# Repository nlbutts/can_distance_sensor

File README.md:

# I'm Not Touching You

This is a small CAN based Time-of-Flight (TOF) sensor. It determines the distance
to an object and sends the resulting message on the CAN bus.

# Design
The block diagram is shown below. The design consists of an input buck regulator.
The regulator should be good up to 24V, but was designed to work at 12V. There
is reverse battery protection, so it should handle accidentially connecting
the battery up in reverse.

The buck generates 5V which is used for the CAN transceiver. The 5V is fed
to two LDO's to generate 3.3V for the processor and 2.8V for the TOF sensor.

There are two status LEDs on the board. An STM32G431 processor powers everything.

There are three user accessible connectors:
Main J3:
| Pin | Use |
| -- | -- |
| 1 | Power |
| 2 | Ground |
| 3 | CAN High |
| 4 | CAN Low |

The mate is a **JST PHR-4**

There is a standard USB Micro B connector that connects to a PC. It enumerates
as a serial port.

# Software
The software uses the STM32CubeIDE to build the code. I really wanted to use CMake with the CubeMX tool,
but I was having trouble getting the code to work correctly. So CudeIDE for the win.

The code is SUPER simple. It just reads the TOF sensor once every 100 ms and sends out a CAN message.

The CAN message is defined as:
| Byte | Definition |
| ---- | --- |
| 1 | API Status |
| 2-3 | distance in mm |
| 4-5 | ambient Mcps |
| 6-7 | signal Mcps |

The **API Status** is the not well defined. If the value is zero, the distance is valid.
The distance is in millimeters.
The Ambient and Signal values are in Millions of Chips Per Second.

The CAN ID is based on the WPILib CAN interface:

Device Type is Misc (10)
Manufacturer is 20
API Class is Status (5)
API Index is 0
Device Number is currently 0 (need to figure out how to have several of these on the bus)

## SWD Debug
It is assumed you are using a JLink and it is installed in **/opt/SEGGER/JLink**
In the scripts directory:
1) Run **gdbstart.sh** in one terminal
2) Run debug.sh in other terminal. You now have the full power of GDB at your literial finger tips

## Firmware upgrade
There is no ability to upgrade the firmware right now. It will be fixed in future PCB rev.
Currently you have to JTAG/SWD the firmware.

# Potential other parts
STM32G0:
https://jlcpcb.com/partdetail/STMicroelectronics-STM32G0B1CBT6/C2847904
Can we use a M0???

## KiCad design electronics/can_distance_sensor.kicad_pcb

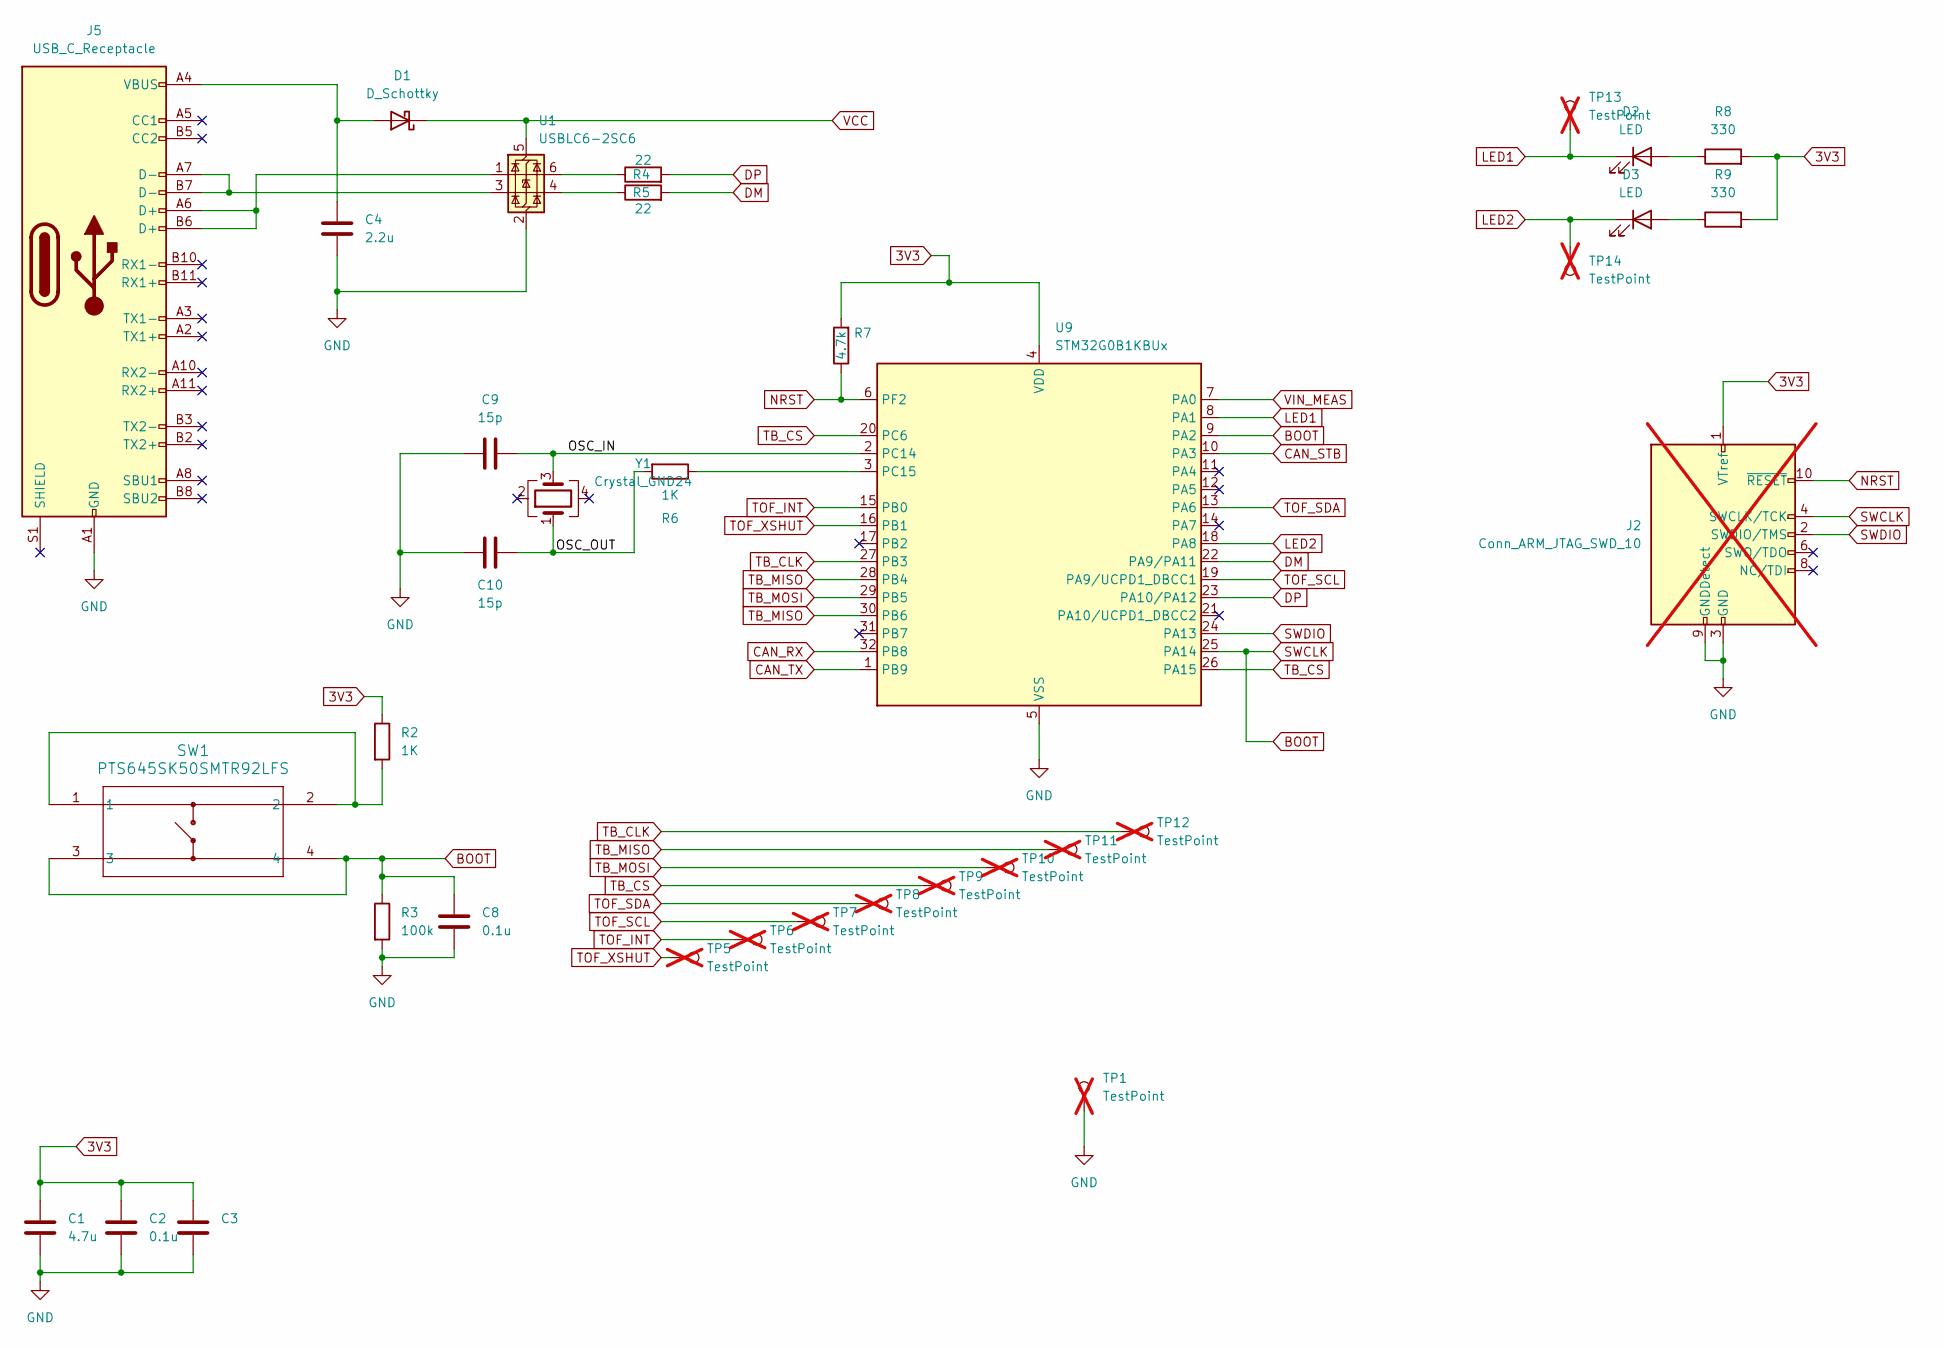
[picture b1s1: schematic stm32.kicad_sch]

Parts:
C1: 4.7u; C_0603_1608Metric; JLCPCB C19666
C2, C3, C8: 0.1u; C_0402_1005Metric; JLCPCB C1525
C4: 2.2u; C_0603_1608Metric; JLCPCB C23630
C9, C10: 15p; C_0402_1005Metric; JLCPCB C1548
D1: D_Schottky; D_SOD-123; Digikey B0540W-FDICT-ND
D2, D3: LED; LED_0603_1608Metric; JLCPCB C2286
J2: Conn_ARM_JTAG_SWD_10; Tag-Connect_TC2050-IDC-NL_2x05_P1.27mm_Vertical_with_bottom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; not fitted
J5: USB_C_Receptacle; CONN_105450-0101_MOL; JLCPCB C134092
R2, R6: 1K; R_0402_1005Metric; JLCPCB C11702
R3: 100k; R_0402_1005Metric; JLCPCB C25741
R4, R5: 22; R_0402_1005Metric; JLCPCB C25092
R7: 4.7k; R_0402_1005Metric; JLCPCB C25900
R8, R9: 330; R_0402_1005Metric; JLCPCB C25104
SW1: PTS645SK50SMTR92LFS; PTS645SK50SMTR92LFS_CNK; JLCPCB C221872
TP1, TP5, TP6, TP7, TP8, TP9, TP10, TP11, TP12, TP13, TP14: TestPoint; TestPoint_Pad_D1.0mm; not fitted
U1: USBLC6-2SC6; SOT-23-6; JLCPCB C7519
U9: STM32G0B1KBUx; QFN-32-1EP_5x5mm_P0.5mm_EP3.45x3.45mm; JLCPCB C5159549
Y1: Crystal_GND24; Crystal_SMD_3225-4Pin_3.2x2.5mm; JLCPCB C156247

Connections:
3V3: C1.1, C2.1, C3.1, J2.1 (VTref), R2.1, R7.2, R8.2, R9.2, U9.4 (VDD); also elsewhere on the board
/STM32/OSC_IN: C9.2, U9.2 (PC14), Y1.3
/STM32/OSC_OUT: C10.2, R6.2, Y1.1
BOOT: C8.1, J2.4 (SWCLK/TCK), R3.1, SW1.3, SW1.4, U9.9 (PA2), U9.25 (PA14)
CAN_RX: U9.32 (PB8); also elsewhere on the board
CAN_STB: U9.10 (PA3); also elsewhere on the board
CAN_TX: U9.1 (PB9); also elsewhere on the board
DM: R5.2, U9.22 (PA9/PA11)
DP: R4.2, U9.23 (PA10/PA12)
GND: C1.2, C2.2, C3.2, C4.1, C8.2, C9.1, C10.1, J2.3 (GND), J2.5 (GND), J2.9 (GNDDetect), J5.A1 (GND), J5.A12 (GND), J5.B1 (GND), J5.B12 (GND), R3.2, TP1.1, U1.2 (GND), U9.5 (VSS), U9.33 (VSS); also elsewhere on the board
LED1: D2.1 (K), TP13.1, U9.8 (PA1)
LED2: D3.1 (K), TP14.1, U9.18 (PA8)
NRST: J2.10 (~RESET), R7.1, U9.6 (PF2)
unnamed: C4.2, D1.2 (A), J5.A4 (VBUS), J5.A9 (VBUS), J5.B4 (VBUS), J5.B9 (VBUS)
unnamed: D2.2 (A), R8.1
unnamed: D3.2 (A), R9.1
unnamed: J5.A6 (D+), J5.B6 (D+), U1.1 (I/O1)
unnamed: J5.A7 (D-), J5.B7 (D-), U1.3 (I/O2)
unnamed: R2.2, SW1.1, SW1.2
unnamed: R4.1, U1.6 (I/O1)
unnamed: R5.1, U1.4 (I/O2)
unnamed: R6.1, U9.3 (PC15)
SWDIO: J2.2 (SWDIO/TMS), U9.24 (PA13)
TB_ABS: TP11.1, U9.28 (PB4), U9.30 (PB6); also elsewhere on the board
TB_CLK: TP12.1, U9.27 (PB3); also elsewhere on the board
TB_CS: TP9.1, U9.20 (PC6), U9.26 (PA15); also elsewhere on the board
TB_MOSI: TP10.1, U9.29 (PB5); also elsewhere on the board
TOF_INT: TP6.1, U9.15 (PB0); also elsewhere on the board
TOF_SCL: TP7.1, U9.19 (PA9/UCPD1_DBCC1); also elsewhere on the board
TOF_SDA: TP8.1, U9.13 (PA6); also elsewhere on the board
TOF_XSHUT: TP5.1, U9.16 (PB1); also elsewhere on the board
VCC: D1.1 (K), U1.5 (VBUS); also elsewhere on the board
VIN_MEAS: U9.7 (PA0); also elsewhere on the board

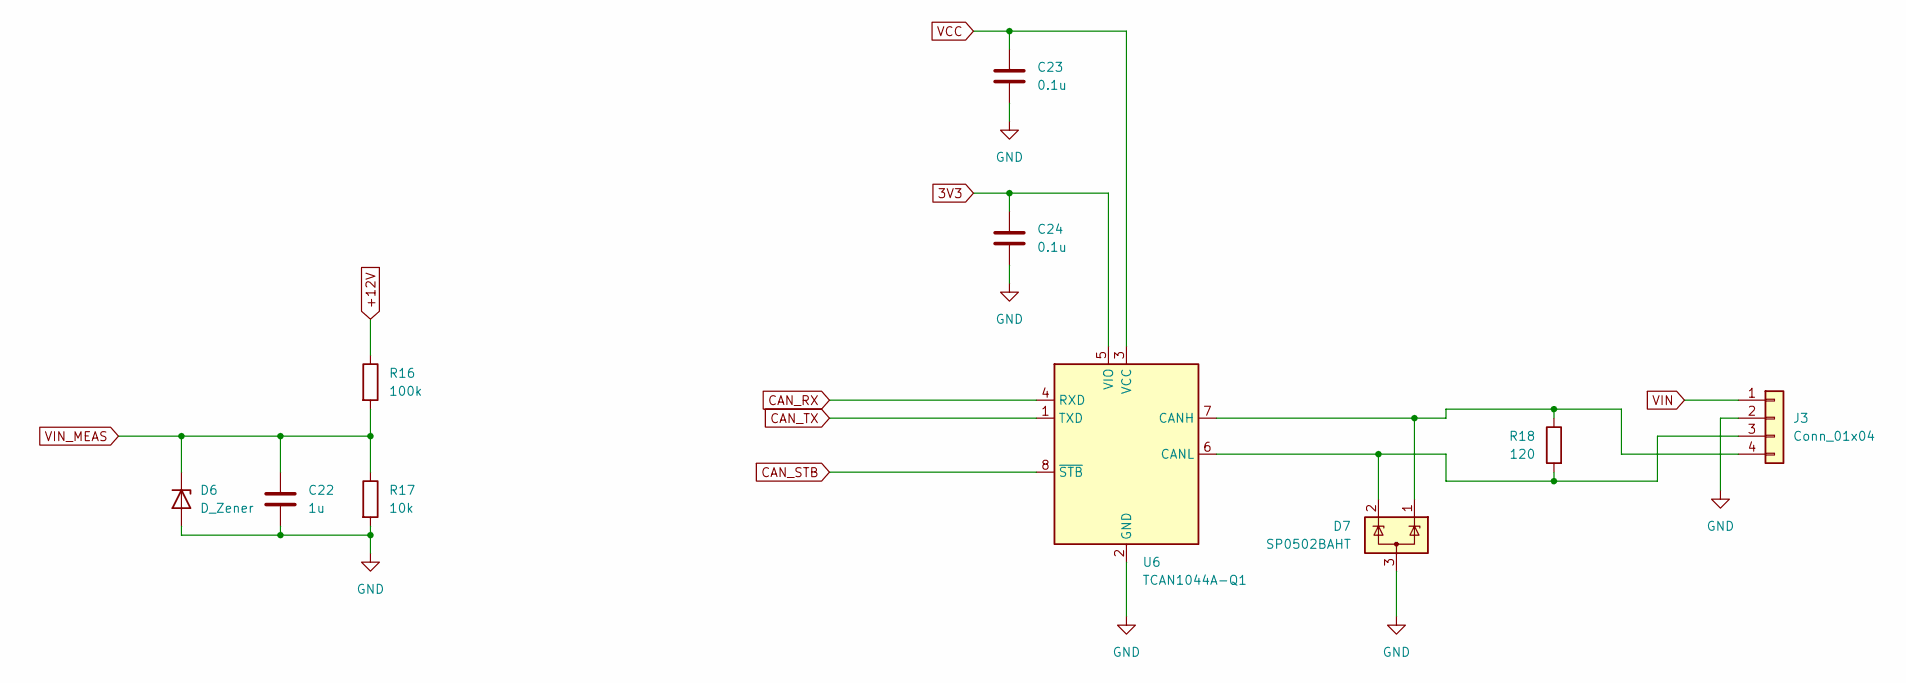
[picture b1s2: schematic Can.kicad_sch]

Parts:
C22: 1u; C_0402_1005Metric; JLCPCB C52923
C23, C24: 0.1u; C_0402_1005Metric; JLCPCB C1525
D6: D_Zener; D_SOD-123; JLCPCB C2105
D7: SP0502BAHT; SOT-23; JLCPCB C32677
J3: Conn_01x04; JST_PH_S4B-PH-K_1x04_P2.00mm_Horizontal; JLCPCB C160354
R16: 100k; R_0402_1005Metric; JLCPCB C25741
R17: 10k; R_0402_1005Metric; JLCPCB C25744
R18: 120; R_0402_1005Metric; JLCPCB C25079
U6: TCAN1044A-Q1; VSON-8-1EP_3x3mm_P0.65mm_EP1.6x2.4mm; JLCPCB C3234119

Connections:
3V3: C24.1, U6.5 (VIO); also elsewhere on the board
+12V: R16.1; also elsewhere on the board
CAN_RX: U6.4 (RXD); also elsewhere on the board
CAN_STB: U6.8 (~STB); also elsewhere on the board
CAN_TX: U6.1 (TXD); also elsewhere on the board
GND: C22.2, C23.2, C24.2, D6.2 (A), D7.3 (A), J3.2, R17.2, U6.2 (GND); also elsewhere on the board
unnamed: D7.2 (K), J3.3, R18.2, U6.6 (CANL)
unnamed: D7.1 (K), J3.4, R18.1, U6.7 (CANH)
VCC: C23.1, U6.3 (VCC); also elsewhere on the board
VIN: J3.1; also elsewhere on the board
VIN_MEAS: C22.1, D6.1 (K), R16.2, R17.1; also elsewhere on the board

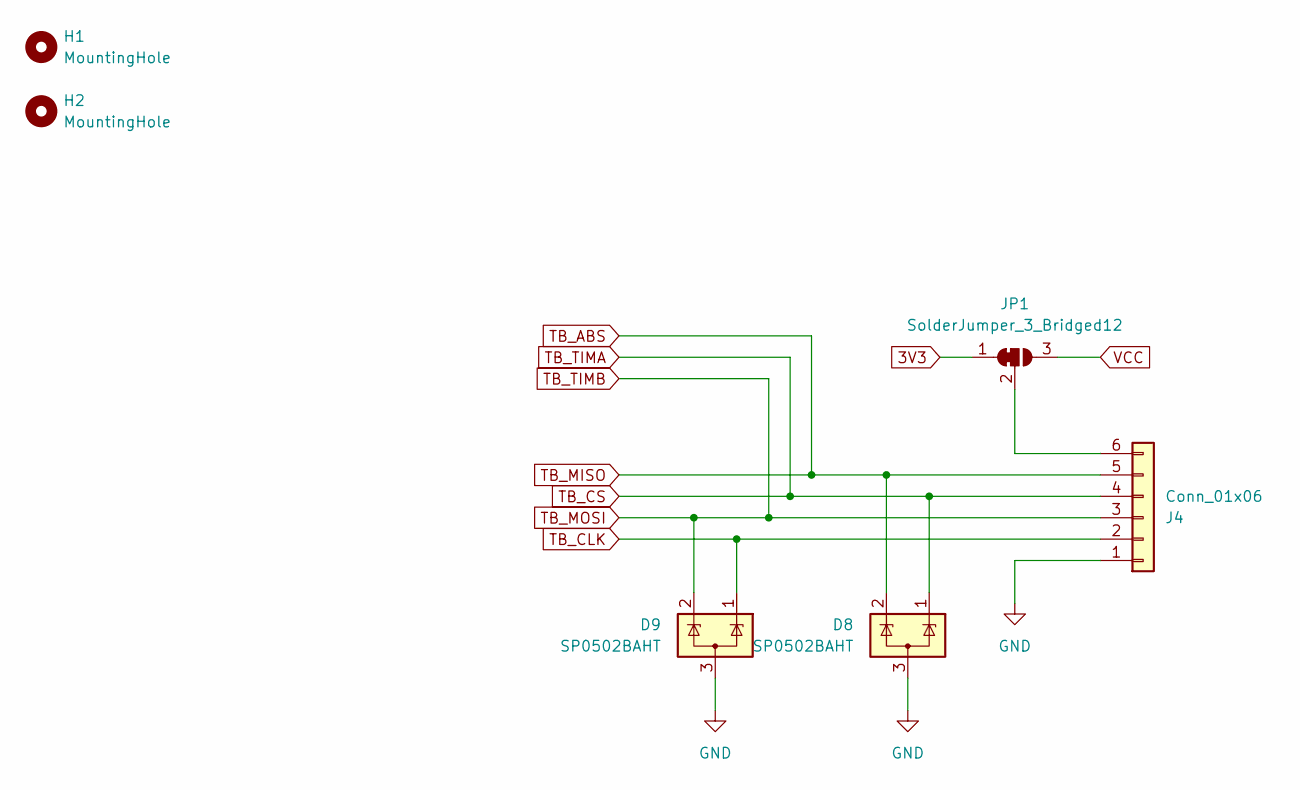
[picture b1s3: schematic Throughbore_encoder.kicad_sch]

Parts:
D8, D9: SP0502BAHT; SOT-23; JLCPCB C32677
H1, H2: MountingHole; MountingHole_2.2mm_M2
J4: Conn_01x06; JST_PH_S6B-PH-K_1x06_P2.00mm_Horizontal; JLCPCB C157920
JP1: SolderJumper_3_Bridged12; SolderJumper-3_P1.3mm_Bridged2Bar12_RoundedPad1.0x1.5mm_Num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

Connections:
3V3: JP1.1 (A); also elsewhere on the board
GND: D8.3 (A), D9.3 (A), J4.1; also elsewhere on the board
unnamed: J4.6, JP1.2 (C)
TB_ABS: D8.2 (K), J4.5; also elsewhere on the board
TB_CLK: D9.1 (K), J4.2; also elsewhere on the board
TB_CS: D8.1 (K), J4.4; also elsewhere on the board
TB_MOSI: D9.2 (K), J4.3; also elsewhere on the board
VCC: JP1.3 (B); also elsewhere on the board

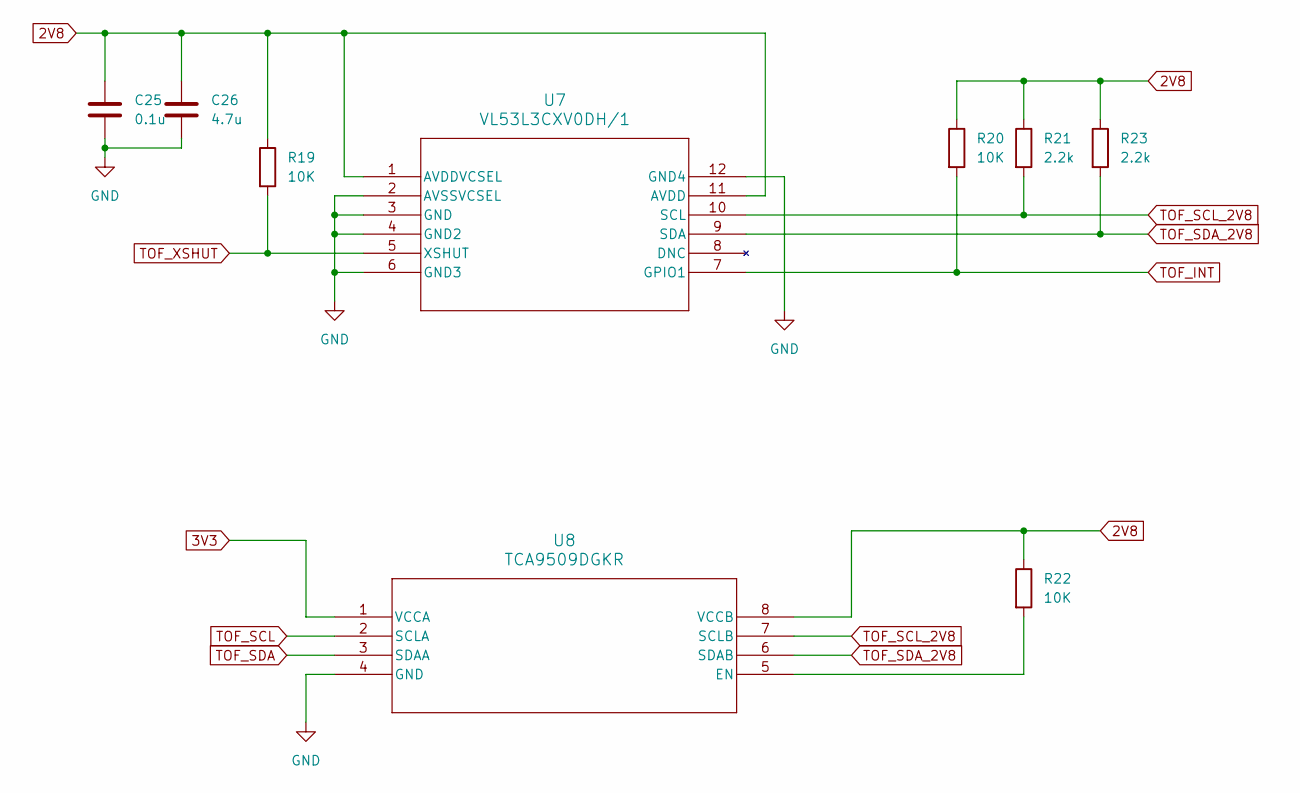
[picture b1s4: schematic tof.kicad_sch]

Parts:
C25: 0.1u; C_0402_1005Metric; JLCPCB C1525
C26: 4.7u; C_0603_1608Metric; JLCPCB C19666
R19, R20, R22: 10K; R_0402_1005Metric; JLCPCB C25744
R21, R23: 2.2k; R_0402_1005Metric; JLCPCB C25879
U7: VL53L3CXV0DH/1; LGA12_STM; JLCPCB C3178291
U8: TCA9509DGKR; DGK8; JLCPCB C478462

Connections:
2V8: C25.1, C26.1, R19.1, R20.1, R21.1, R22.1, R23.1, U7.1 (AVDDVCSEL), U7.11 (AVDD), U8.8 (VCCB); also elsewhere on the board
3V3: U8.1 (VCCA); also elsewhere on the board
GND: C25.2, C26.2, U7.2 (AVSSVCSEL), U7.3 (GND), U7.4 (GND2), U7.6 (GND3), U7.12 (GND4), U8.4 (GND); also elsewhere on the board
unnamed: R22.2, U8.5 (EN)
TOF_INT: R20.2, U7.7 (GPIO1); also elsewhere on the board
TOF_SCL: U8.2 (SCLA); also elsewhere on the board
TOF_SCL_2V8: R21.2, U7.10 (SCL), U8.7 (SCLB)
TOF_SDA: U8.3 (SDAA); also elsewhere on the board
TOF_SDA_2V8: R23.2, U7.9 (SDA), U8.6 (SDAB)
TOF_XSHUT: R19.2, U7.5 (XSHUT); also elsewhere on the board

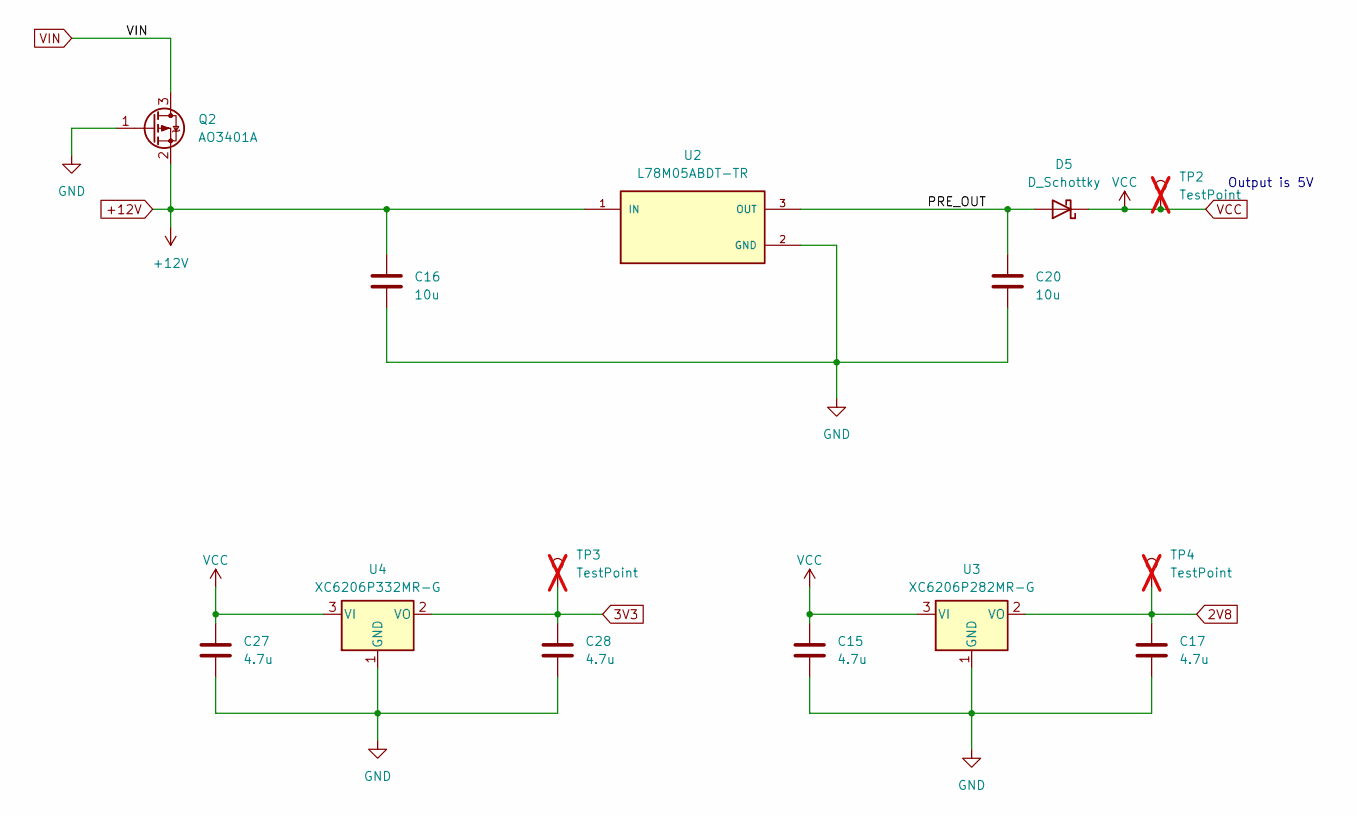
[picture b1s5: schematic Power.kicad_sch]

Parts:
C15, C17, C27, C28: 4.7u; C_0603_1608Metric; JLCPCB C19666
C16, C20: 10u; C_0603_1608Metric; Digikey 490-5523-1-ND
D5: D_Schottky; D_SOD-123; Digikey B0540W-FDICT-ND
Q2: AO3401A; SOT-23; JLCPCB C15127
TP2, TP3, TP4: TestPoint; TestPoint_Pad_D1.0mm; not fitted
U2: L78M05ABDT-TR; VREG_L78M05ABDT-TR; PARTREV 23; JLCPCB C58069
U3: XC6206P282MR-G; SOT-23; JLCPCB C14255
U4: XC6206P332MR-G; SOT-23; JLCPCB C5446

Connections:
2V8: C17.1, TP4.1, U3.2 (VO); also elsewhere on the board
3V3: C28.1, TP3.1, U4.2 (VO); also elsewhere on the board
+12V: C16.1, Q2.2 (S), U2.1 (IN); also elsewhere on the board
/Power/PRE_OUT: C20.1, D5.2 (A), U2.3 (OUT)
GND: C15.2, C16.2, C17.2, C20.2, C27.2, C28.2, Q2.1 (G), U2.2 (GND), U3.1 (GND), U4.1 (GND); also elsewhere on the board
VCC: C15.1, C27.1, D5.1 (K), TP2.1, U3.3 (VI), U4.3 (VI); also elsewhere on the board
VIN: Q2.3 (D); also elsewhere on the board

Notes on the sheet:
Output is 5V

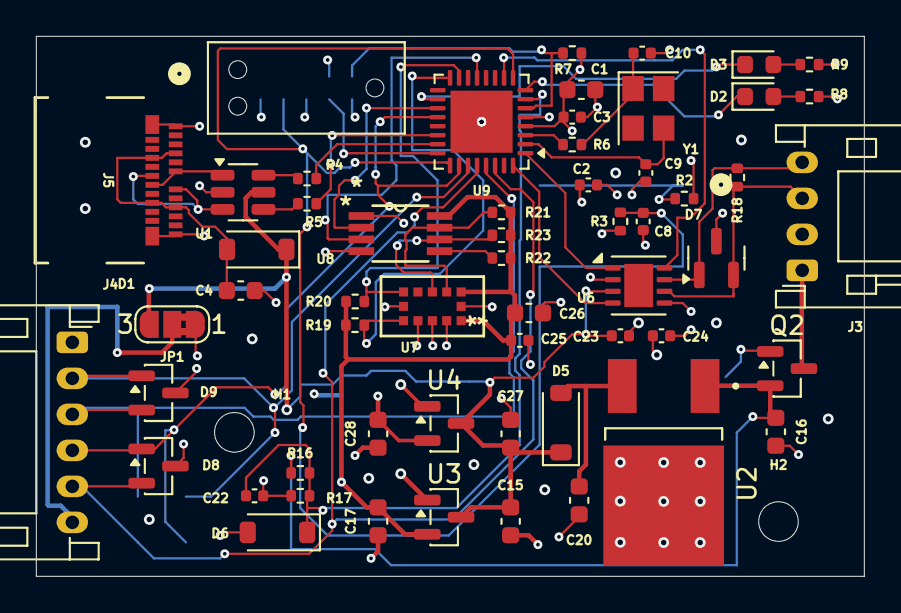
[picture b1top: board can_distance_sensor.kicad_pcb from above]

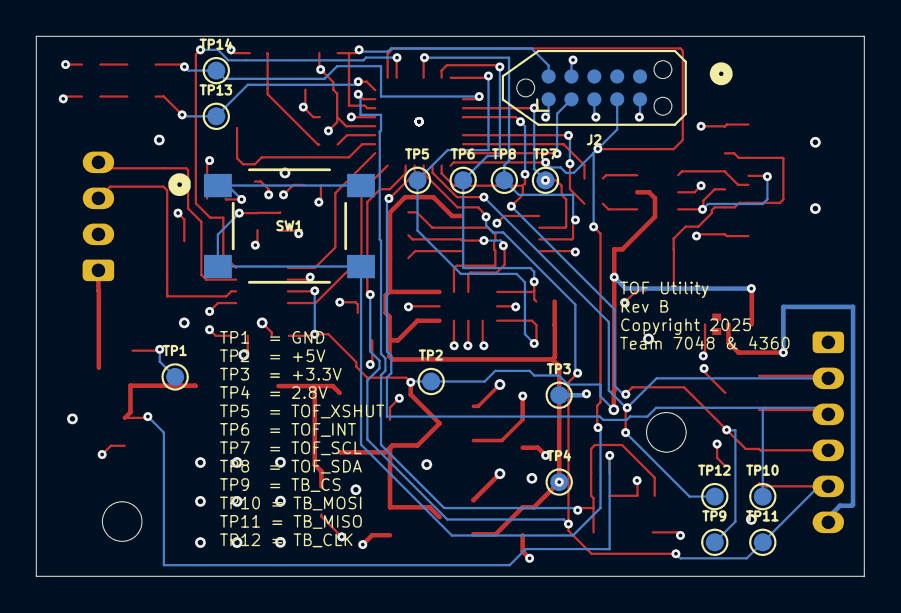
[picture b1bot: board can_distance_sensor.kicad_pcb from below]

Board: 4 copper layers, 46.0 x 30.0 mm, 74 parts (16 on the bottom side), 43 nets.

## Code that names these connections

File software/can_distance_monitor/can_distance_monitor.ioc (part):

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Mcu.Name=STM32G0B1K(B-C-E)Ux
Mcu.Package=UFQFPN32
Mcu.UserName=STM32G0B1KBUx
PA0.Mode=IN0
PA0.Signal=ADC1_IN0
PA1.GPIOParameters=GPIO_Label
PA1.GPIO_Label=LED1
PA1.Signal=GPIO_Output
PA11\ [PA9].Mode=Device
PA11\ [PA9].Signal=USB_DM
PA12\ [PA10].Mode=Device
PA12\ [PA10].Signal=USB_DP
PA13.Mode=Serial_Wire
PA13.Signal=SYS_SWDIO
PA14-BOOT0.Mode=Serial_Wire
PA14-BOOT0.Signal=SYS_SWCLK
PA3.GPIOParameters=GPIO_Label
PA3.GPIO_Label=CAN_STB
PA3.Signal=GPIO_Output
PA4.Mode=Asynchronous
PA4.Signal=USART6_TX
PA5.Mode=Asynchronous
PA5.Signal=USART6_RX
PA6.Mode=I2C
PA6.Signal=I2C2_SDA
PA8.GPIOParameters=GPIO_Label
PA8.GPIO_Label=LED2
PA8.Signal=GPIO_Output
PA9.Mode=I2C
PA9.Signal=I2C2_SCL
PB0.GPIOParameters=GPIO_Label
PB0.GPIO_Label=TOF_INT
PB0.Signal=GPIO_Input
PB1.GPIOParameters=PinState,GPIO_PuPd,GPIO_Label,GPIO_ModeDefaultOutputPP
PB1.GPIO_Label=TOF_XSHUT
PB1.GPIO_ModeDefaultOutputPP=GPIO_MODE_OUTPUT_OD
PB1.GPIO_PuPd=GPIO_NOPULL
PB1.PinState=GPIO_PIN_SET
PB1.Signal=GPIO_Output
PB8.Mode=FDCAN_Activate
PB8.Signal=FDCAN1_RX
PB9.Mode=FDCAN_Activate
PB9.Signal=FDCAN1_TX
PC14-OSC32_IN\ (PC14).Mode=HSE-External-Clock-Source
PC14-OSC32_IN\ (PC14).Signal=RCC_OSC_IN
PC15-OSC32_OUT\ (PC15).Mode=OSC enable
PC15-OSC32_OUT\ (PC15).Signal=RCC_OSC_EN
PC6.Signal=S_TIM3_CH1
RCC.HSE_VALUE=16000000
RCC.SYSCLKFreq_VALUE=64000000
RCC.SYSCLKSource=RCC_SYSCLKSOURCE_PLLCLK
board=custom

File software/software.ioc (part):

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Mcu.Name=STM32F446R(C-E)Tx
Mcu.Package=LQFP64
Mcu.UserName=STM32F446RETx
PA0-WKUP.Signal=ADCx_IN0
PA1.Signal=ADCx_IN1
PA10.GPIOParameters=GPIO_Label
PA10.GPIO_Label=ID
PA10.Signal=GPIO_Input
PA11.Mode=Device_Only
PA11.Signal=USB_OTG_FS_DM
PA12.Mode=Device_Only
PA12.Signal=USB_OTG_FS_DP
PA13.Mode=Serial_Wire
PA13.Signal=SYS_JTMS-SWDIO
PA14.Mode=Serial_Wire
PA14.Signal=SYS_JTCK-SWCLK
PA2.Signal=ADCx_IN2
PB0.GPIOParameters=GPIO_Label
PB0.GPIO_Label=CAN_STB
PB0.Signal=GPIO_Output
PB1.GPIOParameters=GPIO_Label
PB1.GPIO_Label=CAN_FAULT
PB1.Signal=GPIO_Input
PB2.GPIOParameters=GPIO_Label
PB2.GPIO_Label=CAN_WAKE
PB2.Signal=GPIO_Output
PB4.GPIOParameters=GPIO_Label
PB4.GPIO_Label=SW
PB4.Signal=GPIO_Input
PB6.Mode=I2C
PB6.Signal=I2C1_SCL
PB7.Mode=I2C
PB7.Signal=I2C1_SDA
PB8.Mode=CAN_Activate
PB8.Signal=CAN1_RX
PB9.Mode=CAN_Activate
PB9.Signal=CAN1_TX
PC5.GPIOParameters=GPIO_Label
PC5.GPIO_Label=CAN_EN
PC5.Signal=GPIO_Output
PC6.GPIOParameters=GPIO_Label
PC6.GPIO_Label=SPARE4
PC6.Signal=GPIO_Input
PC7.GPIOParameters=GPIO_Label
PC7.GPIO_Label=SPARE3
PC7.Signal=GPIO_Input
PC8.GPIOParameters=GPIO_Label
PC8.GPIO_Label=SPARE2
PC8.Signal=GPIO_Input
PC9.GPIOParameters=GPIO_Label
PC9.GPIO_Label=SPARE1
PC9.Signal=GPIO_Input
PH0-OSC_IN.Mode=HSE-External-Oscillator
PH0-OSC_IN.Signal=RCC_OSC_IN
PH1-OSC_OUT.Mode=HSE-External-Oscillator
PH1-OSC_OUT.Signal=RCC_OSC_OUT
RCC.HSE_VALUE=16000000
RCC.SYSCLKFreq_VALUE=168000000
board=custom

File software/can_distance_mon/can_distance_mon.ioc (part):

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Mcu.Name=STM32G431C(6-8-B)Ux
Mcu.Package=UFQFPN48
Mcu.UserName=STM32G431CBUx
PA0.GPIOParameters=GPIO_Label
PA0.GPIO_Label=VIN_MEAS
PA0.Mode=IN1-Single-Ended
PA0.Signal=ADC1_IN1
PA11.Mode=Device
PA11.Signal=USB_DM
PA12.Mode=Device
PA12.Signal=USB_DP
PA13.Mode=Serial_Wire
PA13.Signal=SYS_JTMS-SWDIO
PA14.Mode=Serial_Wire
PA14.Signal=SYS_JTCK-SWCLK
PA15.Mode=I2C
PA15.Signal=I2C1_SCL
PA5.GPIOParameters=GPIO_Label
PA5.GPIO_Label=BUTTON
PA5.Signal=GPIO_Input
PA6.GPIOParameters=GPIO_Label
PA6.GPIO_Label=LED2
PA6.Signal=GPIO_Output
PA7.GPIOParameters=GPIO_Label
PA7.GPIO_Label=LED1
PA7.Signal=GPIO_Output
PB14.Mode=Full_Duplex_Master
PB14.Signal=SPI2_MISO
PB15.Mode=Full_Duplex_Master
PB15.Signal=SPI2_MOSI
PB5.Signal=GPXTI5
PB6.GPIOParameters=GPIO_Label
PB6.GPIO_Label=TOF_XSHUT
PB6.Signal=GPIO_Output
PB7.Mode=I2C
PB7.Signal=I2C1_SDA
PB8-BOOT0.Mode=FDCAN_Activate
PB8-BOOT0.Signal=FDCAN1_RX
PB9.Mode=FDCAN_Activate
PB9.Signal=FDCAN1_TX
PC13.GPIOParameters=GPIO_Label
PC13.GPIO_Label=CAN_STB
PC13.Signal=GPIO_Output
PF0-OSC_IN.Mode=NSS_Signal_Hard_Output
PF0-OSC_IN.Signal=SPI2_NSS
PF1-OSC_OUT.Mode=Full_Duplex_Master
PF1-OSC_OUT.Signal=SPI2_SCK
RCC.HSE_VALUE=16000000
RCC.SYSCLKFreq_VALUE=160000000
RCC.SYSCLKSource=RCC_SYSCLKSOURCE_PLLCLK
board=custom

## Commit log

2024-11-24 Initial checkin.
2024-11-24 Switched to a lower cost TOF sensor.
2024-11-29 Ordered this version.
2025-01-01 Commiting the STM32CudeIDE Software.
2025-01-01 Updated the docs.
2025-01-20 Updated the code and added free rtos.
2025-02-23 Added a version string and optimized the TOF for close distances.
2025-10-13 Pulled in the latest ST code. Started work on next rev.
2025-10-17 Added a stat printing task.
2025-10-18 Major refactor to rev B
2025-10-18 Checked in more files.
2025-10-18 Was going to order this, but 5 boards is 50.
2025-10-20 Added the BOM
2025-10-23 Refactored the design to use basic parts.
2025-10-23 This part was ordered
2025-12-11 Refactoring for new IDE tools and everything.
2025-12-21 Updated to the latest STM32CubeMX and now using STM32CubeIDE for VS Code.
2025-12-21 This code is at least reading the sensor.
2025-12-27 Finished testing the hardware. Decided to change architecture.
2025-12-28 Added a buffered TX system.
2025-12-28 Moved the USB code to a location that won't be overwriten by STM32CubeMX. Added the TOF code back in.

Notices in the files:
electronics/can_distance_sensor.kicad_pcb:
Copyright 2025
